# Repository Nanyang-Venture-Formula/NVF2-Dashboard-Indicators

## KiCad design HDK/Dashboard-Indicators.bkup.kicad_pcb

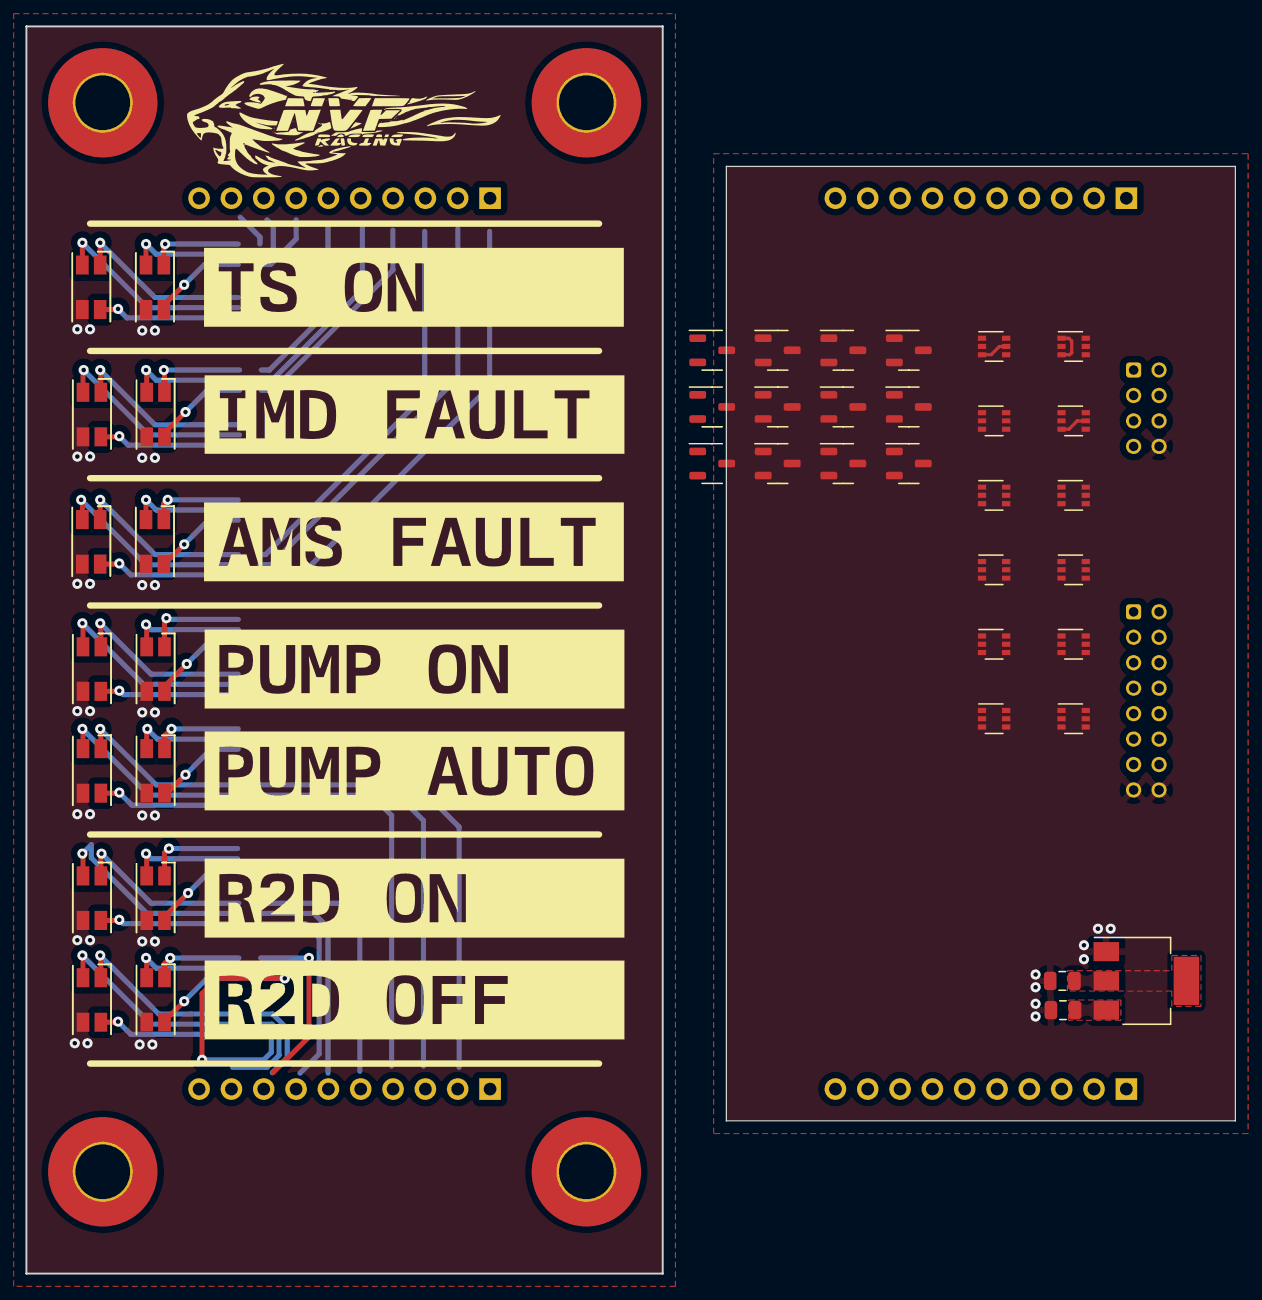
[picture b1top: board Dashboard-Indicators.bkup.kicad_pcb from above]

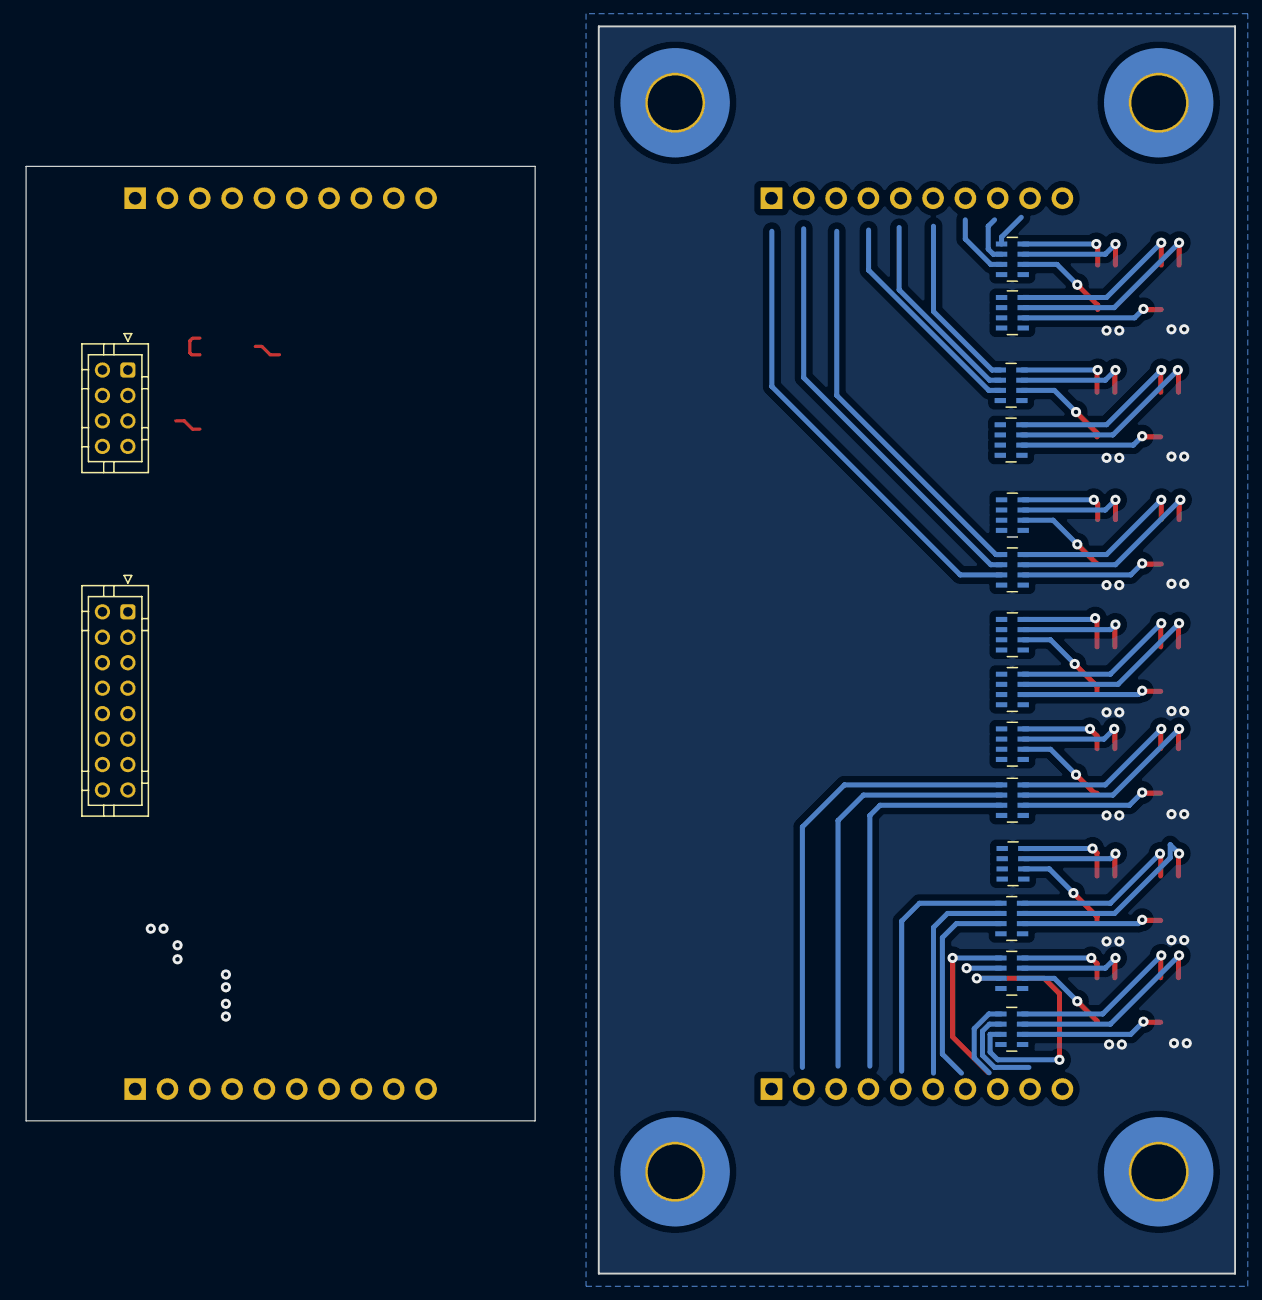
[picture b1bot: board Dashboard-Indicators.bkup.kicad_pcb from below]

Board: 2 copper layers, 95.0 x 98.0 mm, 64 parts (16 on the bottom side), 88 nets.

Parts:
C101, C102: 1u; C_0805_2012Metric
D201, D202, D301, D302, D401, D402, D501, D502, D601, D602, D701, D702, D801, D802: RGB LED; LED_RGB_1210
J101: Conn_02x08_Odd_Even; JST_PHD_B16B-PHDSS_2x08_P2.00mm_Vertical
J102: Conn_02x04_Odd_Even; JST_PHD_B8B-PHDSS_2x04_P2.00mm_Vertical
Q101, Q102, Q103: AO3401A; SOT-23-3
Q104, Q105, Q106, Q107, Q108, Q109, Q110, Q111, Q112: AO3400A; SOT-23-3
RN201, RN202, RN301, RN302, RN401, RN402, RN501, RN502, RN601, RN602, RN701, RN702, RN801, RN802: 47; R_Array_Concave_4x0603
U104: AMS1117-5.0; SOT-223-3_TabPin2
U901, U1001, U1101, U1401, U1501, U1601, U1801, U1901, U2001, U2101, U2201, U2301: 74LVC1G57; SOT-363_SC-70-6
kibuzzard-65B612BA: G***; kibuzzard-65B612BA
kibuzzard-65B612BF: G***; kibuzzard-65B612BF
kibuzzard-65B612C4: G***; kibuzzard-65B612C4
kibuzzard-65B6145B: G***; kibuzzard-65B6145B
kibuzzard-65B61402: G***; kibuzzard-65B61402
kibuzzard-65B61406: G***; kibuzzard-65B61406
kibuzzard-65B61451: G***; kibuzzard-65B61451

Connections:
+5V: C101.1, J101.1, Q112.1 (D), U104.2 (VO), U901.5 (VCC), U1001.5 (VCC), U1101.3 (IN_A), U1101.5 (VCC), U1401.3 (IN_A), U1401.5 (VCC), U1501.5 (VCC), U1601.5 (VCC), U1801.5 (VCC), U1901.5 (VCC), U2001.3 (IN_A), U2001.5 (VCC), U2101.3 (IN_A), U2101.5 (VCC), U2201.3 (IN_A), U2201.5 (VCC), U2301.3 (IN_A), U2301.5 (VCC)
+5VD: Q101.1 (D), Q102.1 (D), Q103.1 (D), Q104.1 (D), Q105.1 (D), Q106.1 (D), Q107.1 (D), Q108.1 (D), Q109.1 (D), Q110.1 (D), Q111.1 (D), Q112.3 (S)
/AMS_FLT: J102.2, U1801.6 (IN_C), U2001.6 (IN_C)
/AMS_FLTLED: Q103.3 (S), RN401.2 (R1), RN402.2 (R1)
/AMS_FLT_LED: Q106.2 (G), Q106.3 (S), RN401.1 (R1.2), RN402.1 (R1.2), U2001.4 (Y)
/AMS_FLT_N: J102.4, U1801.1 (IN_B), U1801.3 (IN_A)
/AND1/INA: U901.3 (IN_A), U1001.4 (Y), U2101.1 (IN_B)
/AND1/OUT: Q101.2 (G), U2101.4 (Y)
/AND2/INA: U1501.3 (IN_A), U1601.4 (Y), U2201.1 (IN_B)
/AND2/OUT: Q102.2 (G), U2201.4 (Y)
/AND3/INA: U1801.4 (Y), U1901.3 (IN_A), U2301.1 (IN_B)
/AND3/OUT: Q103.2 (G), U2301.4 (Y)
/FAULT_LED: RN701.2 (R1), RN702.2 (R1), RN801.2 (R1), RN802.2 (R1)
/IMD_FLT: J102.5, U1401.6 (IN_C), U1601.6 (IN_C)
/IMD_FLTLED: Q102.3 (S), RN301.2 (R1), RN302.2 (R1)
/IMD_FLT_LED: Q105.2 (G), Q105.3 (S), RN301.1 (R1.2), RN302.1 (R1.2), U1401.4 (Y)
/IMD_FLT_N: J102.7, U1601.1 (IN_B), U1601.3 (IN_A)
/INDIC_CNTRL: J101.14, Q112.2 (G)
/INDIC_PULSE1: J101.12, U2101.6 (IN_C), U2201.6 (IN_C), U2301.6 (IN_C)
/Indicator-AMS/RED: RN401.3 (R3.2), RN402.3 (R3.2)
/Indicator-IMD/RED: RN301.3 (R3.2), RN302.3 (R3.2)
/Indicator-PUMP_AUTO/RED: RN801.3 (R3.2), RN802.3 (R3.2)
/Indicator-PUMP_ON/RED: RN701.3 (R3.2), RN702.3 (R3.2)
/Indicator-R2D_OFF/RED: RN601.3 (R3.2), RN602.3 (R3.2)
/Indicator-R2D_ON/RED: RN501.3 (R3.2), RN502.3 (R3.2)
/Indicator-TSAC/RED: RN201.3 (R3.2), RN202.3 (R3.2)
/PUMP_AUTO: J101.6, Q111.2 (G)
/PUMP_AUTO_LED: Q111.3 (S), RN801.1 (R1.2), RN802.1 (R1.2)
/PUMP_ON: J101.4, Q110.2 (G)
/PUMP_ON_LED: Q110.3 (S), RN701.1 (R1.2), RN702.1 (R1.2)
/R2D_OFF: J101.7, Q109.2 (G)
/R2D_OFF_LED: Q109.3 (S), RN601.1 (R1.2), RN602.1 (R1.2)
/R2D_OFF_SW: J101.11, J101.13
/R2D_ON: J101.3, Q107.2 (G)
/R2D_ON_LED: Q107.3 (S), RN501.1 (R1.2), RN502.1 (R1.2)
/R2D_RDY: J101.5, Q108.2 (G)
/R2D_RDY_LED: Q108.3 (S), RN501.2 (R1), RN502.2 (R1), RN601.2 (R1), RN602.2 (R1)
/SCS_CHK1/AND/INA: U1401.1 (IN_B), U1501.4 (Y)
/SCS_CHK2/AND/INA: U1901.4 (Y), U2001.1 (IN_B)
/SCS_CHK/AND/INA: U901.4 (Y), U1101.1 (IN_B)
/TS_FLTLED: Q101.3 (S), RN201.2 (R1), RN202.2 (R1)
/TS_ON: J102.1, U1001.6 (IN_C), U1101.6 (IN_C)
/TS_ON_LED: Q104.2 (G), Q104.3 (S), RN201.1 (R1.2), RN202.1 (R1.2), U1101.4 (Y)
/TS_ON_N: J102.3, U1001.1 (IN_B), U1001.3 (IN_A)
GND: C101.2, C102.2, D201.3 (K), D202.3 (K), D301.3 (K), D302.3 (K), D401.3 (K), D402.3 (K), D501.3 (K), D502.3 (K), D601.3 (K), D602.3 (K), D701.3 (K), D702.3 (K), D801.3 (K), D802.3 (K), J101.15, J101.16, J102.8, U104.1 (GND), U901.1 (IN_B), U901.2 (GND), U901.6 (IN_C), U1001.2 (GND), U1101.2 (GND), U1401.2 (GND), U1501.1 (IN_B), U1501.2 (GND), U1501.6 (IN_C), U1601.2 (GND), U1801.2 (GND), U1901.1 (IN_B), U1901.2 (GND), U1901.6 (IN_C), U2001.2 (GND), U2101.2 (GND), U2201.2 (GND), U2301.2 (GND)
unnamed: D201.1 (BA), RN201.8 (R1.2)
unnamed: D201.2 (GA), RN201.7 (R2.2)
unnamed: D201.4 (RA), RN201.6 (R3.2)
unnamed: D202.1 (BA), RN202.8 (R1.2)
unnamed: D202.2 (GA), RN202.7 (R2.2)
unnamed: D202.4 (RA), RN202.6 (R3.2)
unnamed: D301.1 (BA), RN301.8 (R1.2)
unnamed: D301.2 (GA), RN301.7 (R2.2)
unnamed: D301.4 (RA), RN301.6 (R3.2)
unnamed: D302.1 (BA), RN302.8 (R1.2)
unnamed: D302.2 (GA), RN302.7 (R2.2)
unnamed: D302.4 (RA), RN302.6 (R3.2)
unnamed: D401.1 (BA), RN401.8 (R1.2)
unnamed: D401.2 (GA), RN401.7 (R2.2)
unnamed: D401.4 (RA), RN401.6 (R3.2)
unnamed: D402.1 (BA), RN402.8 (R1.2)
unnamed: D402.2 (GA), RN402.7 (R2.2)
unnamed: D402.4 (RA), RN402.6 (R3.2)
unnamed: D501.1 (BA), RN501.8 (R1.2)
unnamed: D501.2 (GA), RN501.7 (R2.2)
unnamed: D501.4 (RA), RN501.6 (R3.2)
unnamed: D502.1 (BA), RN502.8 (R1.2)
unnamed: D502.2 (GA), RN502.7 (R2.2)
unnamed: D502.4 (RA), RN502.6 (R3.2)
unnamed: D601.1 (BA), RN601.8 (R1.2)
unnamed: D601.2 (GA), RN601.7 (R2.2)
unnamed: D601.4 (RA), RN601.6 (R3.2)
unnamed: D602.1 (BA), RN602.8 (R1.2)
unnamed: D602.2 (GA), RN602.7 (R2.2)
unnamed: D602.4 (RA), RN602.6 (R3.2)
unnamed: D701.1 (BA), RN701.8 (R1.2)
unnamed: D701.2 (GA), RN701.7 (R2.2)
unnamed: D701.4 (RA), RN701.6 (R3.2)
unnamed: D702.1 (BA), RN702.8 (R1.2)
unnamed: D702.2 (GA), RN702.7 (R2.2)
unnamed: D702.4 (RA), RN702.6 (R3.2)
unnamed: D801.1 (BA), RN801.8 (R1.2)
unnamed: D801.2 (GA), RN801.7 (R2.2)
unnamed: D801.4 (RA), RN801.6 (R3.2)
unnamed: D802.1 (BA), RN802.8 (R1.2)
unnamed: D802.2 (GA), RN802.7 (R2.2)
unnamed: D802.4 (RA), RN802.6 (R3.2)
VCC: C102.1, J101.2, J102.6, U104.3 (VI)

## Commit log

2024-01-23 Initialize gh-pages
2024-01-23 Moving files docs/* LICENSE using main
2024-01-23 refactored
2024-01-23 Deploying to gh-pages from @ Nanyang-Venture-Formula/NVF2-Dashboard-Indicators@3467ed069c9dc707a4d236061b36be0cdb1cdb87 🚀
2024-01-23 Deploying to gh-pages from @ Nanyang-Venture-Formula/NVF2-Dashboard-Indicators@75e1dcecc3b92d00f494f29aace60ea84af85221 🚀
2024-01-24 updated WIP
2024-01-24 updated ignore
2024-01-24 Deploying to gh-pages from @ Nanyang-Venture-Formula/NVF2-Dashboard-Indicators@742877f2a019a80df034cca2827d5648ac5e33a6 🚀
2024-01-24 rm files
2024-01-24 Deploying to gh-pages from @ Nanyang-Venture-Formula/NVF2-Dashboard-Indicators@9d0b6a56d2c6616705d6d0a4bb15c442f3a5cae1 🚀
2024-01-24 Deploying to gh-pages from @ Nanyang-Venture-Formula/NVF2-Dashboard-Indicators@91470b6e29241b22dddee4e6af9c38ed83feb7ef 🚀
2024-01-24 updated gitignore
2024-01-24 Deploying to gh-pages from @ Nanyang-Venture-Formula/NVF2-Dashboard-Indicators@fe737dc350b544d356e084f81a010aa7507258e9 🚀
2024-01-29 added rev1-cancelled
2024-01-29 Deploying to gh-pages from @ Nanyang-Venture-Formula/NVF2-Dashboard-Indicators@0c1ca8f294148aaa34c0bf50b0a4bbb2ac0e1077 🚀
2024-02-01 updated rev2 complete
2024-02-01 Deploying to gh-pages from @ Nanyang-Venture-Formula/NVF2-Dashboard-Indicators@3b6ca0c22a13f66cf7122865271f147c00f8bc42 🚀
2024-02-23 final-archive
